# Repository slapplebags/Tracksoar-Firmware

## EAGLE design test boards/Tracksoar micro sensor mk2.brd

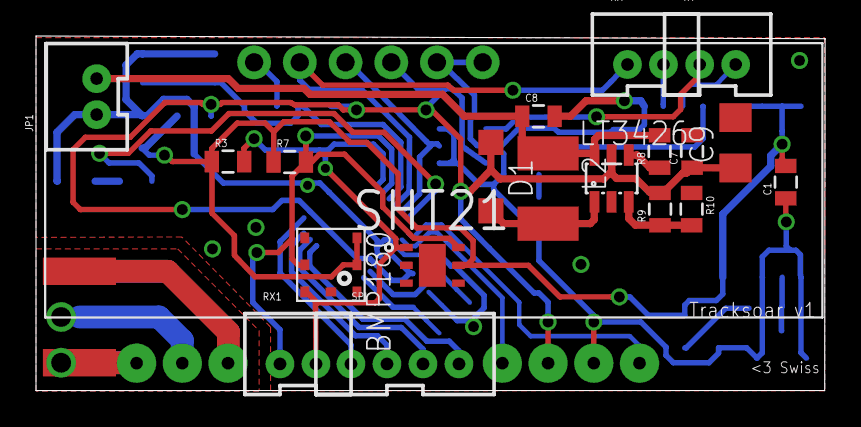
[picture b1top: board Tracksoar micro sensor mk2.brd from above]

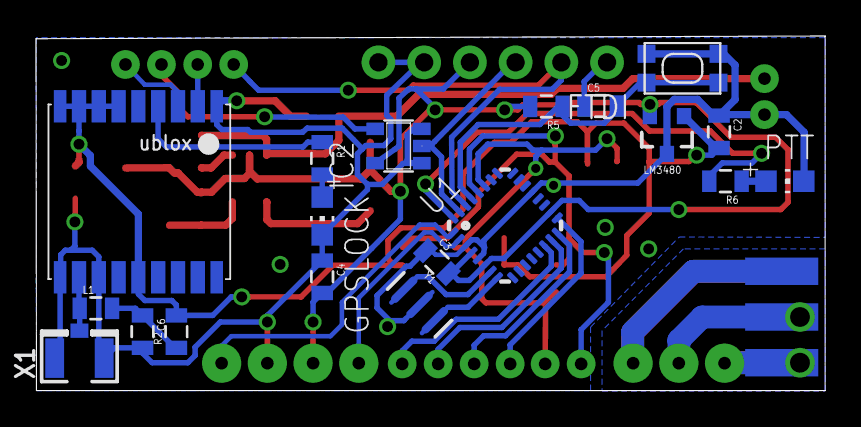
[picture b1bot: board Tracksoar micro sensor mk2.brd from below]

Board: 2 copper layers, 43.8 x 19.7 mm, 42 parts (21 on the bottom side), 31 nets.

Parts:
BMP180: BMP180
C1, C2, C3, C4, C5: .1uf; 0805
C6: 47pf; 0805
C7: 22uf; 0805
C8: 10uf; 0805
C9: 100uf; C1206
D1: MBR120VLSFT1; SOD123
FRAME1: FRAME-LETTER; CREATIVE_COMMONS
FTDI: 1X06_NO_SILK
GPSLOCK: CHIP-LED0805
IC2: 74AHC1G125DBV; SOT23-5
J$1: SMA_EDGE; SMA-EDGE
JP1: M02JST-PTH-VERT; JST-2-PTH-VERT
L1: 27nh; 0805
L2: 2.2uh; L1812
LM3480: LM3480IM4; SOT23-3
LT3426: LT3426; SOT23-6
PTT: CHIP-LED0805
R1: 100ohm; 0805
R2: 10ohm; 0805
R3, R7: 4.7k; 0805
R5: 10k; 0805
R6: 330ohm; 0805
R8: 1m; 0805
R9: 95.3k; 0805
R10: 30.9k; 0805
RX, RX1: RX; JST-2-PTH-VERT
SHT21: SHT21; DFN300X300X110-7N
SPI: JST-4-PTH-VERT
SW1: SPST_TACT-KMR2; KMR2
TX: TX; JST-2-PTH-VERT
U1: ATMEGA168MLF; MLF32
U$1: UBLOX_MAX
U$2: RADIOMETRIX-HX1
X1: U.FL
Y1: 16MHZ; RESONATOR-SMD

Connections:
3V: BMP180.2, BMP180.3, C1.2, C2.2, LM3480.1, R2.2, R3.1, R7.1, SHT21.5, U$1.6_V_BCKP, U$1.7_VCC_IO, U$1.8_VCC, U$1.9_V_RESET, U$1.14_VCC_RF
15V: C8.1, JP1.2, L2.1, LT3426.6, R8.2
D3: U1.1, U$2.TXD
D4: U1.2, U$2.EN
DTR: C5.1, FTDI.1
GND: BMP180.7, C1.1, C2.1, C3.1, C4.1, C6.2, C7.2, C8.2, C9.2, FTDI.5, FTDI.6, GPSLOCK.C, IC2.1, IC2.3, J$1.GND@0, J$1.GND@1, J$1.GND@2, J$1.GND@3, JP1.1, LM3480.3, LT3426.2, PTT.C, R10.1, SHT21.2, SW1.2, SW1.4, U1.3, U1.5, U1.21, U$1.1_GND, U$1.10_GND, U$1.12_GND, U$2.0V, U$2.RFGND, U$2.RFGND2, X1.1, X1.2, Y1.2
LED: R6.2, U1.32
MISO: SPI.2, U1.16
MOSI: SPI.3, U1.15
unnamed: J$1.SIG, U$2.RFOUT
unnamed: GPSLOCK.A, R1.2
unnamed: L1.1, U$1.11_RF_IN, X1.3
unnamed: D1.A, L2.2, LT3426.1
unnamed: LT3426.4, R8.1
unnamed: LT3426.3, R9.1, R10.2
unnamed: U1.8, Y1.3
unnamed: C5.2, R5.1, SW1.1, SW1.3, U1.29
unnamed: C6.1, L1.2, R2.1
unnamed: U1.7, Y1.1
unnamed: PTT.A, R6.1
PPS: R1.1, U$1.4_TIMEPULSE
RX: TX.2, U$1.3_RXD1
RXO: FTDI.2, RX.1, U1.30
SCK: SPI.1, U1.17
SCL: BMP180.5, R7.2, RX1.1, SHT21.6, U1.28
SDA: BMP180.6, R3.2, RX1.2, SHT21.1, U1.27
SS: SPI.4, U1.14
TX: RX.2, U$1.2_TXD1
TX1: IC2.4, TX.1
TXO: FTDI.3, IC2.2, U1.31
VCC: C3.2, C4.2, C7.1, C9.1, D1.C, FTDI.4, IC2.5, LM3480.2, LT3426.5, R5.2, R9.2, U1.4, U1.6, U1.18, U$2.VCC

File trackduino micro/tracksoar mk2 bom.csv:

"Part";"Value";"Device";"Package";"Description";"MPN";"OC_FARNELL";"OC_NEWARK";"PACKAGE";"PROD_ID";"SUPPLIER";"VALUE";
"BMP180";"BMP180";"BMP180";"BMP180";"BOSCH BMP180 DIGITAL BAROMETRIC PRESSURE SENSOR";"";"";"";"";"";"";"";
"C1";".1uf";"CAP0805";"0805";"Capacitor";"";"";"";"";"";"";"";
"C2";".1uf";"CAP0805";"0805";"Capacitor";"";"";"";"";"";"";"";
"C3";".1uf";"CAP0805";"0805";"Capacitor";"";"";"";"";"";"";"";
"C4";".1uf";"CAP0805";"0805";"Capacitor";"";"";"";"";"";"";"";
"C5";".1uf";"CAP0805";"0805";"Capacitor";"";"";"";"";"";"";"";
"C7";"22uf";"CAP0805";"0805";"Capacitor";"";"";"";"";"";"";"";
"C8";"10uf";"CAP0805";"0805";"Capacitor";"";"";"";"";"";"";"";
"C9";"100uf";"C-USC1206";"C1206";"CAPACITOR, American symbol";"";"";"";"";"";"";"";
"D1";"MBR120VLSFT1";"DIODE-SOD123";"SOD123";"DIODE";"";"";"";"";"";"";"";
"FRAME1";"FRAME-LETTER";"FRAME-LETTER";"CREATIVE_COMMONS";"Schematic Frame";"";"";"";"";"";"";"";
"FTDI";"";"M06NO_SILK_FEMALE_PTH";"1X06_NO_SILK";"Header 6";"";"";"";"";"CONN-08437";"";"";
"IC2";"74AHC1G125DBV";"74AHC1G125DBV";"SOT23-5";"Single Bus Buffer Gate with 3-State Output";"";"";"";"";"";"";"";
"J$1";"SMA_EDGE";"SMA_EDGE";"SMA-EDGE";"SMA Antenna Connector";"";"";"";"";"";"";"";
"JP1";"M02JST-PTH-VERT";"M02JST-PTH-VERT";"JST-2-PTH-VERT";"Standard 2-pin 0.1" header. Use with";"";"";"";"";"";"";"";
"L2";"2.2uh";"L-USL1812";"L1812";"INDUCTOR, American symbol";"";"";"";"";"";"";"";
"LED1";"";"LEDCHIP-LED0805";"CHIP-LED0805";"LED";"";"";"";"";"";"";"";
"LM3480";"LM3480IM4";"LM3480IM4";"SOT23-3";"Small package linear regulator";"";"";"";"";"";"";"";
"LT3426";"LT3426";"LT3426";"SOT23-6";"LT3426";"";"";"";"";"";"";"";
"PTT";"";"LEDCHIP-LED0805";"CHIP-LED0805";"LED";"";"";"";"";"";"";"";
"R1";"100ohm";"RESISTOR0805-RES";"0805";"Resistor";"";"";"";"";"";"";"";
"R3";"4.7k";"RESISTOR0805-RES";"0805";"Resistor";"";"";"";"";"";"";"";
"R5";"10k";"RESISTOR0805-RES";"0805";"Resistor";"";"";"";"";"";"";"";
"R6";"330ohm";"RESISTOR0805-RES";"0805";"Resistor";"";"";"";"";"";"";"";
"R7";"4.7k";"RESISTOR0805-RES";"0805";"Resistor";"";"";"";"";"";"";"";
"R8";"1m";"RESISTOR0805-RES";"0805";"Resistor";"";"";"";"";"";"";"";
"R9";"95.3k";"RESISTOR0805-RES";"0805";"Resistor";"";"";"";"";"";"";"";
"R10";"30.9k";"RESISTOR0805-RES";"0805";"Resistor";"";"";"";"";"";"";"";
"RX";"RX";"M02JST-PTH-VERT";"JST-2-PTH-VERT";"Standard 2-pin 0.1" header. Use with";"";"";"";"";"";"";"";
"SHT21";"SHT21";"SHT21";"DFN300X300X110-7N";"SENSOR, HUMIDITY & TEMP";"SHT21";"1855468";"20T1172";"DFN-6";"";"SENSIRION";"";
"SPI";"";"M04JST-PTH-VERT";"JST-4-PTH-VERT";"Header 4";"";"";"";"";"";"";"";
"SW1";"SPST_TACT-KMR2";"SPST_TACT-KMR2";"KMR2";"SMT 6mm switch, EVQQ2 series";"";"";"";"";"";"";"";
"TX";"TX";"M02JST-PTH-VERT";"JST-2-PTH-VERT";"Standard 2-pin 0.1" header. Use with";"";"";"";"";"";"";"";
"TX1";"TX";"M02JST-PTH-VERT";"JST-2-PTH-VERT";"Standard 2-pin 0.1" header. Use with";"";"";"";"";"";"";"";
"U$1";"UBLOX_MAX";"UBLOX_MAX";"UBLOX_MAX";"UBLOX MAX";"";"";"";"";"";"";"";
"U$2";"RADIOMETRIX-HX1";"RADIOMETRIX-HX1";"RADIOMETRIX-HX1";"";"";"";"";"";"";"";"";
"U$3";"ANTENNA2SMD3";"ANTENNA2SMD3";"ANTENNA-CHIP4";"Chip antenna";"";"";"";"";"";"";"";
"U1";"ATMEGA168MLF";"ATMEGA168MLF";"MLF32";"Atmel 32-pin 8-bit micro, 16k flash.";"";"";"";"";"";"";"";
"Y1";"16MHZ";"RESONATOR16MHZ";"RESONATOR-SMD";"Resonator";"";"";"";"";"XTAL-08900";"";"16MHZ";

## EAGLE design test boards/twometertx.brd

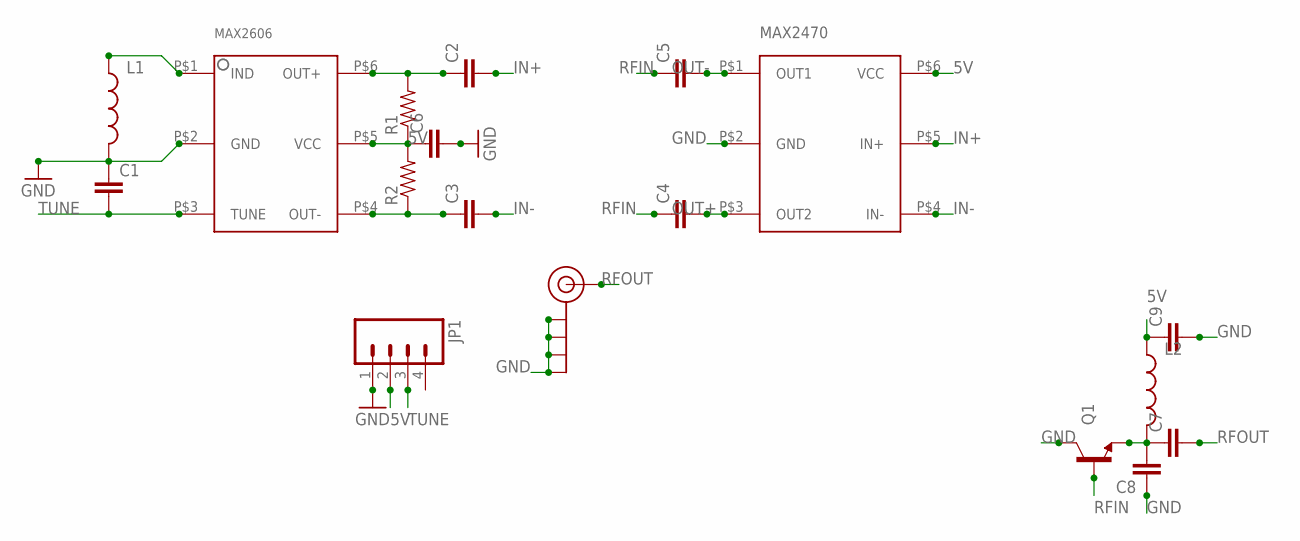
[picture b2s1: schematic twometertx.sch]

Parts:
C1, C2, C3, C4, C5, C6, C7, C8, C9: CAP0805; 0805
J$1: SMA_EDGE; SMA-EDGE
JP1: M04LONGPADS; 1X04_LONGPADS
L1, L2: INDUCTOR0805; 0805
Q1: TRANSISTOR_NPNSOT89; SOT89
R1, R2: RESISTOR0805-RES; 0805
U$1: MAX2606
U$2: MAX2470

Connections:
5V: C6.1, C9.1, JP1.2, L2.1, R1.1, R2.2, U$1.P$5 (VCC), U$2.P$6 (VCC)
GND: C1.1, C6.2, C8.1, C9.2, J$1.GND@0 (GND), J$1.GND@1 (GND), J$1.GND@2 (GND), J$1.GND@3 (GND), JP1.1, L1.2, Q1.2 (C), U$1.P$2 (GND), U$2.P$2 (GND)
IN+: C2.2, U$2.P$5 (IN+)
IN-: C3.2, U$2.P$4 (IN-)
unnamed: L1.1, U$1.P$1 (IND)
unnamed: C7.1, C8.2, L2.2, Q1.3 (E)
OUT+: C4.2, U$2.P$3 (OUT2)
OUT-: C5.2, U$2.P$1 (OUT1)
RFIN: C4.1, C5.1, Q1.1 (B)
RFOUT: C7.2, J$1.SIG (SIGNAL)
THING: C2.1, R1.2, U$1.P$6 (OUT+)
THING2: C3.1, R2.1, U$1.P$4 (OUT-)
TUNE: C1.2, JP1.3, U$1.P$3 (TUNE)

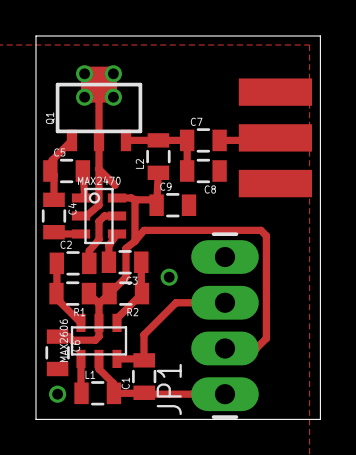
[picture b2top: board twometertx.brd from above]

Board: 2 copper layers, 15.8 x 21.3 mm, 18 parts (0 on the bottom side), 13 nets.

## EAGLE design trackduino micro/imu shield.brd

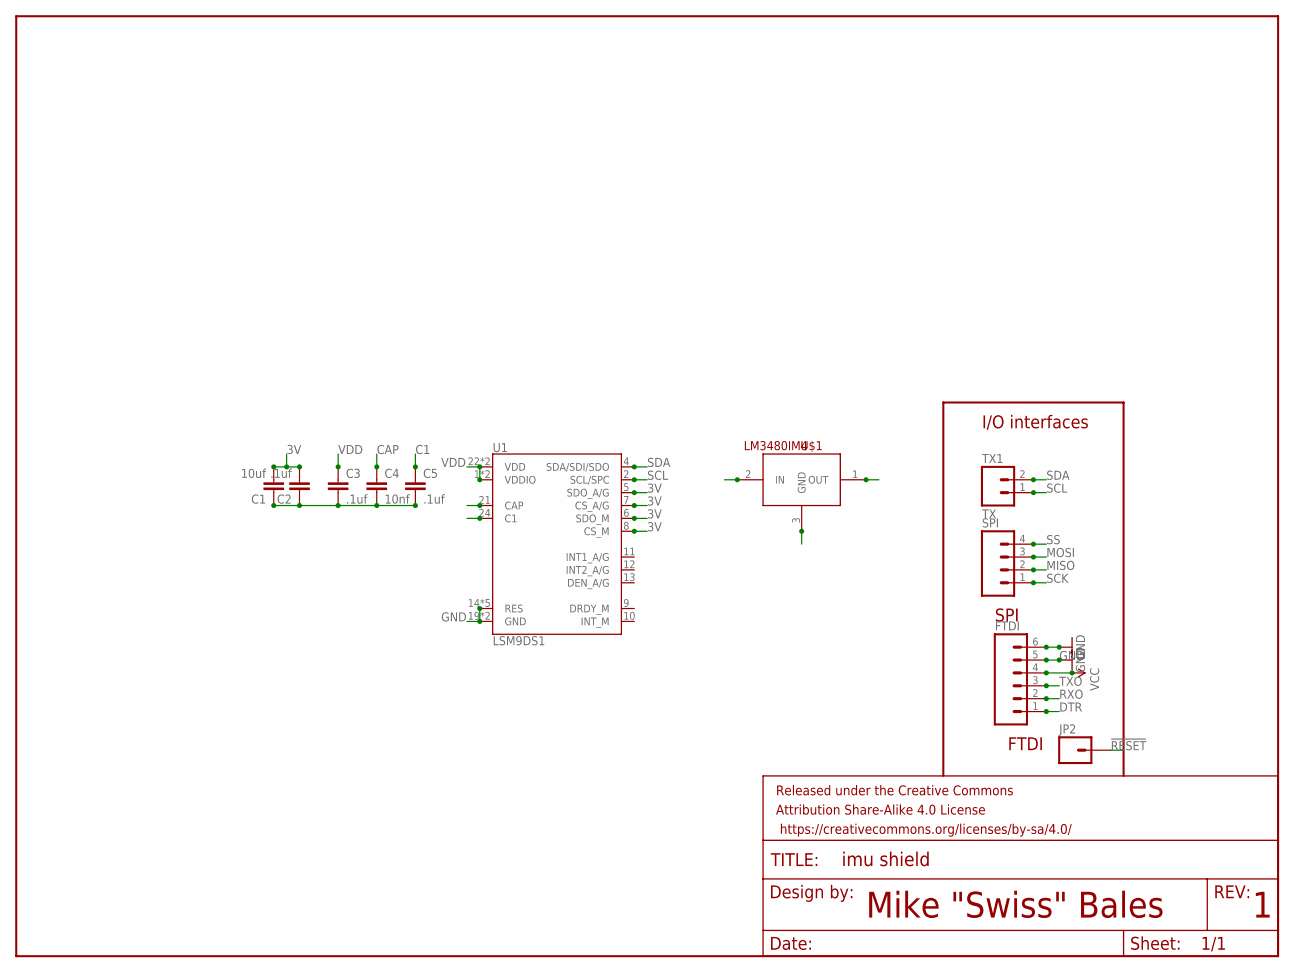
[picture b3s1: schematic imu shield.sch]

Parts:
C1: 10uf; 0805
C2, C3, C5: .1uf; 0805
C4: 10nf; 0805
FRAME1: FRAME-LETTER; CREATIVE_COMMONS
FTDI: M06NO_SILK_FEMALE_PTH; 1X06_NO_SILK
JP2: M01PTH; 1X01
SPI: M04JST-PTH-VERT; JST-4-PTH-VERT
TX1: TX; JST-2-PTH-VERT
U1: LSM9DS1; LGA24-8X4
U$1: LM3480IM4; SOT23-3

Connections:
3V: C1.2, C2.2, U1.5 (SDO_A/G), U1.6 (SDO_M), U1.7 (CS_A/G), U1.8 (CS_M)
!RESET: JP2.1
C1: C5.1, U1.24 (C1)
CAP: C4.1, U1.21 (CAP)
DTR: FTDI.1
GND: FTDI.5, FTDI.6, U1.14 (RES), U1.15 (RES), U1.16 (RES), U1.17 (RES), U1.18 (RES), U1.19 (GND), U1.20 (GND), U$1.3 (GND)
MISO: SPI.2
MOSI: SPI.3
unnamed: C1.1, C2.1, C3.2, C4.2, C5.2
RXO: FTDI.2
SCK: SPI.1
SCL: TX1.1, U1.2 (SCL/SPC)
SDA: TX1.2, U1.4 (SDA/SDI/SDO)
SS: SPI.4
TXO: FTDI.3
VCC: FTDI.4, U$1.2 (IN)
VDD: C3.1, U1.1 (VDDIO), U1.3 (VDDIO), U1.22 (VDD), U1.23 (VDD), U$1.1 (OUT)

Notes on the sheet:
Mike "Swiss" Bales
I/O interfaces
SPI
FTDI

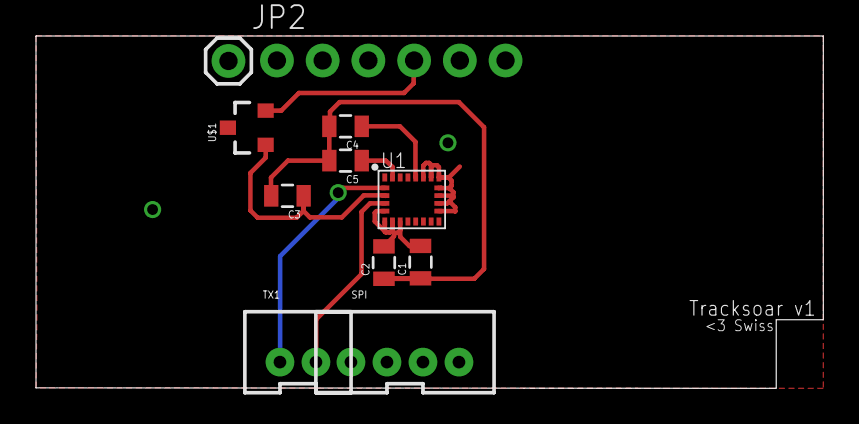
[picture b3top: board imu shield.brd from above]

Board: 2 copper layers, 43.7 x 19.6 mm, 12 parts (1 on the bottom side), 9 nets.

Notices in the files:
parts and their libraries:
SparkFun-PowerIC: Licensing: Creative Commons ShareAlike 4.0 International - https://creativecommons.org/licenses/by-sa/4.0
SparkFun-Aesthetics: Released under the Creative Commons Attribution Share-Alike 4.0 License
SparkFun-Aesthetics: https://creativecommons.org/licenses/by-sa/4.0
